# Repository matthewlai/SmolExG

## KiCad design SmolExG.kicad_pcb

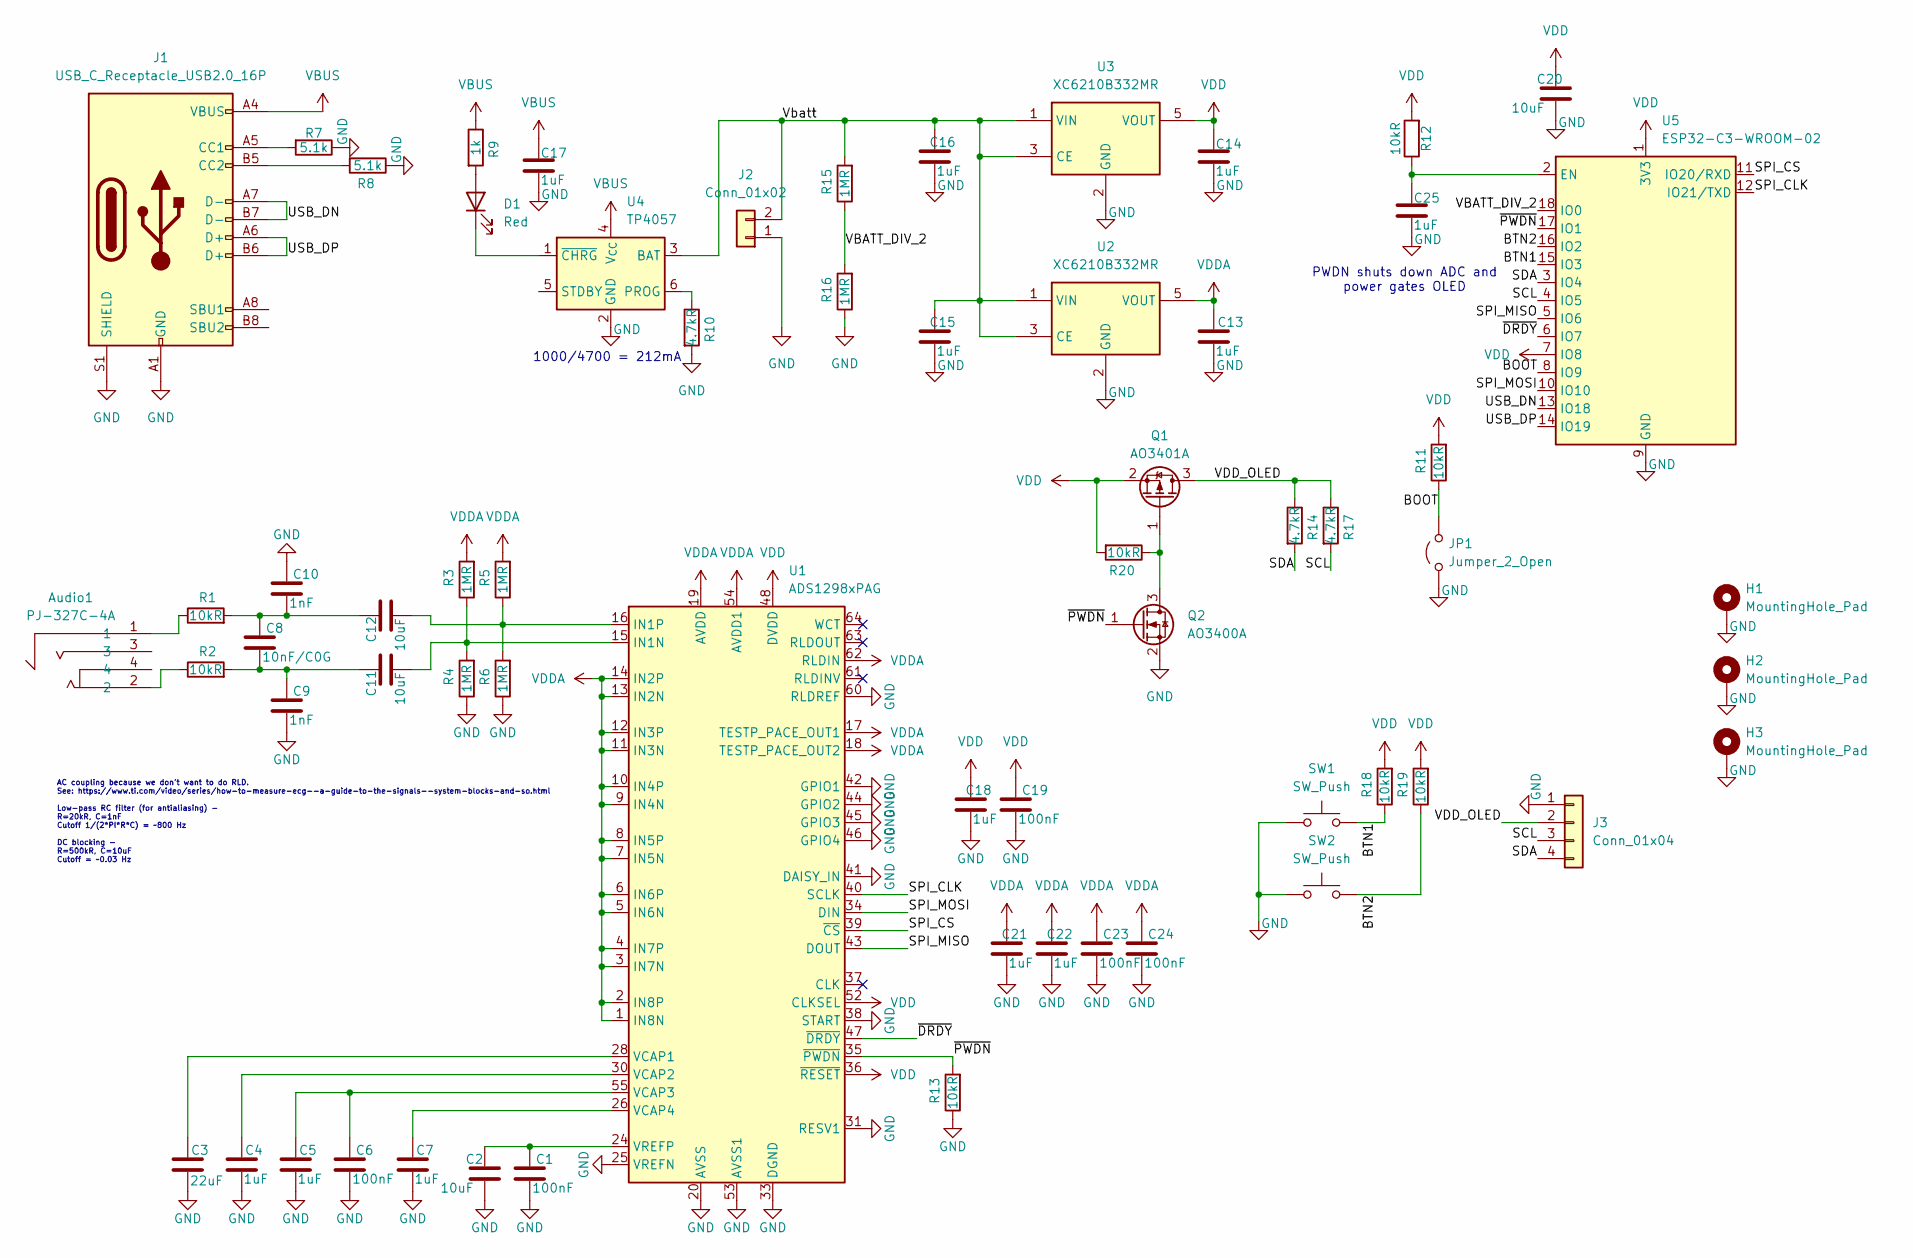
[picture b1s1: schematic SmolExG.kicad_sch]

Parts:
Audio1: PJ-327C-4A; AUDIO-SMD_PJ-327C-4A; LCSC Part C145813
C1, C6, C19, C23, C24: 100nF; C_0402_1005Metric; LCSC C1525
C2, C11, C12, C20: 10uF; C_0402_1005Metric; LCSC C15525
C3: 22uF; C_0805_2012Metric; LCSC C45783
C4, C5, C7, C13, C14, C15, C16, C17, C18, C21, C22, C25: 1uF; C_0402_1005Metric; LCSC C52923
C8: 10nF/C0G; C_0402_1005Metric; LCSC C36911359
C9, C10: 1nF; C_0402_1005Metric; LCSC C1523
D1: Red; LED_0603_1608Metric; LCSC C2286
H1, H2, H3: MountingHole_Pad; MountingHole_2.2mm_M2_Pad_Via
J1: USB_C_Receptacle_USB2.0_16P; USB_C_Receptacle_HRO_TYPE-C-31-M-12; LCSC C165948
J2: Conn_01x02; CONN-SMD_B2B-PH-SM4-TB-LF-SN; LCSC C265003
J3: Conn_01x04; PinHeader_1x04_P2.54mm_Vertical
JP1: Jumper_2_Open; PinHeader_1x02_P2.54mm_Vertical
Q1: AO3401A; SOT-23; LCSC C15127
Q2: AO3400A; SOT-23; LCSC C20917
R1, R2, R11, R12, R13, R18, R19, R20: 10kR; R_0402_1005Metric; LCSC C25744
R3, R4, R5, R6, R15, R16: 1MR; R_0402_1005Metric; LCSC C26083
R7, R8: 5.1k; R_0402_1005Metric; LCSC C25905
R9: 1k; R_0402_1005Metric; LCSC C11702
R10, R14, R17: 4.7kR; R_0402_1005Metric; LCSC C25900
SW1, SW2: SW_Push; SW_Push_1P1T_XKB_TS-1187A; LCSC C318884
U1: ADS1298xPAG; TQFP-64_10x10mm_P0.5mm; LCSC C527440
U2, U3: XC6210B332MR; SOT-23-5; LCSC C3021084
U4: TP4057; TSOT-23-6
U5: ESP32-C3-WROOM-02; LCSC C2934560

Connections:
/BOOT: JP1.2 (B), R11.1, U5.8 (IO9)
/BTN1: R18.1, SW1.2, U5.15 (IO3)
/BTN2: R19.1, SW2.2, U5.16 (IO2)
/SCL: J3.3, R17.2, U5.4 (IO5)
/SDA: J3.4, R14.2, U5.3 (IO4)
/SPI_CLK: U1.40 (SCLK), U5.12 (IO21/TXD)
/SPI_CS: U1.39 (~CS), U5.11 (IO20/RXD)
/SPI_MISO: U1.43 (DOUT), U5.5 (IO6)
/SPI_MOSI: U1.34 (DIN), U5.10 (IO10)
/USB_DN: J1.A7 (D-), J1.B7 (D-), U5.13 (IO18)
/USB_DP: J1.A6 (D+), J1.B6 (D+), U5.14 (IO19)
/VBATT_DIV_2: R15.1, R16.2, U5.18 (IO0)
/VDD_OLED: J3.2, Q1.3 (D), R14.1, R17.1
/Vbatt: C15.2, C16.2, J2.2, R15.2, U2.1 (VIN), U2.3 (CE), U3.1 (VIN), U3.3 (CE), U4.3 (BAT)
/~DRDY: U1.47 (~DRDY), U5.6 (IO7)
/~PWDN: Q2.1 (G), R13.2, U1.35 (~PWDN), U5.17 (IO1)
GND: C1.2, C2.2, C3.1, C4.1, C5.1, C6.2, C7.1, C9.2, C10.1, C13.1, C14.1, C15.1, C16.1, C17.1, C18.1, C19.2, C20.2, C21.1, C22.1, C23.2, C24.2, C25.1, H1.1, H2.1, H3.1, J1.A1 (GND), J1.A12 (GND), J1.B1 (GND), J1.B12 (GND), J1.S1 (SHIELD), J2.1, J3.1, JP1.1 (A), Q2.2 (S), R4.1, R6.1, R7.1, R8.1, R10.2, R13.1, R16.1, SW1.1, SW2.1, U1.20 (AVSS), U1.23 (AVSS), U1.25 (VREFN), U1.31 (RESV1), U1.32 (AVSS), U1.33 (DGND), U1.38 (START), U1.41 (DAISY_IN), U1.42 (GPIO1), U1.44 (GPIO2), U1.45 (GPIO3), U1.46 (GPIO4), U1.49 (DGND), U1.51 (DGND), U1.53 (AVSS1), U1.57 (AVSS), U1.58 (AVSS), U1.60 (RLDREF), U2.2 (GND), U3.2 (GND), U4.2 (GND), U5.9 (GND), U5.19 (GND)
unnamed: Audio1.1, R1.1
unnamed: Audio1.2, R2.1
unnamed: C8.1, C10.2, C12.2, R1.2
unnamed: C8.2, C9.1, C11.2, R2.2
unnamed: D1.2 (A), R9.2
unnamed: D1.1 (K), U4.1 (~CHRG)
unnamed: J1.A5 (CC1), R7.2
unnamed: J1.B5 (CC2), R8.2
unnamed: Q1.1 (G), Q2.3 (D), R20.1
unnamed: C11.1, R3.1, R4.2, U1.15 (IN1N)
unnamed: C12.1, R5.1, R6.2, U1.16 (IN1P)
unnamed: C3.2, U1.28 (VCAP1)
unnamed: C4.2, U1.30 (VCAP2)
unnamed: C5.2, C6.1, U1.55 (VCAP3)
unnamed: C7.2, U1.26 (VCAP4)
unnamed: C1.1, C2.1, U1.24 (VREFP)
unnamed: R10.1, U4.6 (PROG)
unnamed: C25.2, R12.1, U5.2 (EN)
VBUS: C17.2, J1.A4 (VBUS), J1.A9 (VBUS), J1.B4 (VBUS), J1.B9 (VBUS), R9.1, U4.4 (V_{CC})
VDD: C14.2, C18.2, C19.1, C20.1, Q1.2 (S), R11.2, R12.2, R18.2, R19.2, R20.2, U1.36 (~RESET), U1.48 (DVDD), U1.50 (DVDD), U1.52 (CLKSEL), U3.5 (VOUT), U5.1 (3V3), U5.7 (IO8)
VDDA: C13.2, C21.2, C22.2, C23.1, C24.1, R3.2, R5.2, U1.1 (IN8N), U1.2 (IN8P), U1.3 (IN7N), U1.4 (IN7P), U1.5 (IN6N), U1.6 (IN6P), U1.7 (IN5N), U1.8 (IN5P), U1.9 (IN4N), U1.10 (IN4P), U1.11 (IN3N), U1.12 (IN3P), U1.13 (IN2N), U1.14 (IN2P), U1.17 (TESTP_PACE_OUT1), U1.18 (TESTP_PACE_OUT2), U1.19 (AVDD), U1.21 (AVDD), U1.22 (AVDD), U1.54 (AVDD1), U1.56 (AVDD), U1.59 (AVDD), U1.62 (RLDIN), U2.5 (VOUT)

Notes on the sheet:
1000/4700 = 212mA
PWDN shuts down ADC and power gates OLED
AC coupling because we don't want to do RLD. See: https://www.ti.com/video/series/how-to-measure-ecg--a-guide-to-the-signals--system-blocks-and-so.html Low-pass RC filter (for antialiasing) - R=20kR, C=1nF Cutoff 1/(2*PI*R*C) = ~800 Hz DC blocking - R=500kR, C=10uF Cutoff = ~0.03 Hz

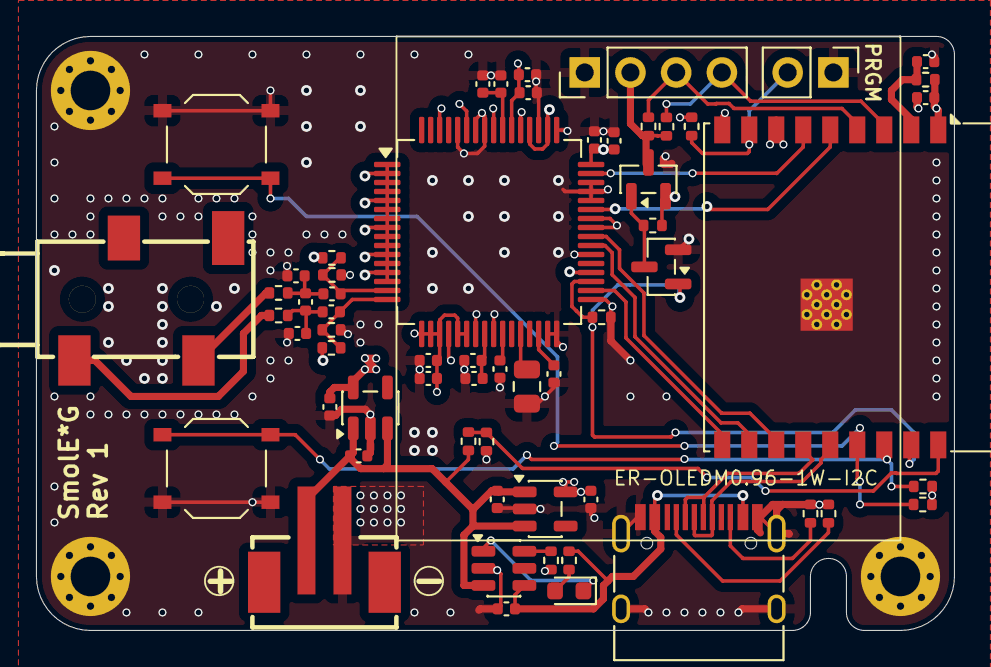
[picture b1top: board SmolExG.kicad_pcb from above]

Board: 4 copper layers, 51.0 x 33.0 mm, 63 parts (0 on the bottom side), 38 nets.

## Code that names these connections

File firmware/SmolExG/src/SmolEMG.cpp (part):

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const FilterCoeffType* FIR_FILTER = FILTER_20_500;
const int FIR_FILTER_TAPS = sizeof(FILTER_20_500) / sizeof(*FILTER_20_500);

constexpr int PWDN_PIN = 1;
constexpr int BUTTON_1_PIN = 3;
constexpr int BUTTON_2_PIN = 2;
constexpr int VBATT_DIV_2_PIN = 0;

constexpr int ADS1298_CS_PIN = 20;
constexpr int ADS1298_DO_PIN = 10;
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void go_to_sleep() {
  // Power gate ADC and display.
  display.setPowerSave(true);
  digitalWrite(PWDN_PIN, LOW);
  delay(100);
  esp_deep_sleep_start();
}
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  // Actually, from my one test chip, the value seems to be
  // around 116nA, though there may be leakage elsewhere.
  constexpr float EST_LEAKAGE = 116e-9f;
  float vbatt_raw = analogReadMilliVolts(VBATT_DIV_2_PIN) / 1000.0f;
  float leakage_r_eq = vbatt_raw / EST_LEAKAGE;
  float low_r_eq = 1.0f / (1.0f / 1e6f + 1.0f / leakage_r_eq);
  float vbatt_est = (low_r_eq + 1e6f) / low_r_eq * vbatt_raw;
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  Serial.begin();

  // Set up pin modes and instantiate debouncer.
  pinMode(PWDN_PIN, OUTPUT);
  pinMode(VBATT_DIV_2_PIN, INPUT);
  pinMode(ADS1298_DRDY_PIN, INPUT);
  ButtonManager btn1(BUTTON_1_PIN);
  ButtonManager btn2(BUTTON_2_PIN);

  // Enable power to the ADC and OLED display.
  digitalWrite(PWDN_PIN, HIGH);

  // Wait a bit for the ADC and display to power up.
  // ADS1298 needs 2^18 internal clocks (t_por), which
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
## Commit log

2026-03-28 Implemented FFT view
2026-04-08 Implement TCP server for ADC data stream
